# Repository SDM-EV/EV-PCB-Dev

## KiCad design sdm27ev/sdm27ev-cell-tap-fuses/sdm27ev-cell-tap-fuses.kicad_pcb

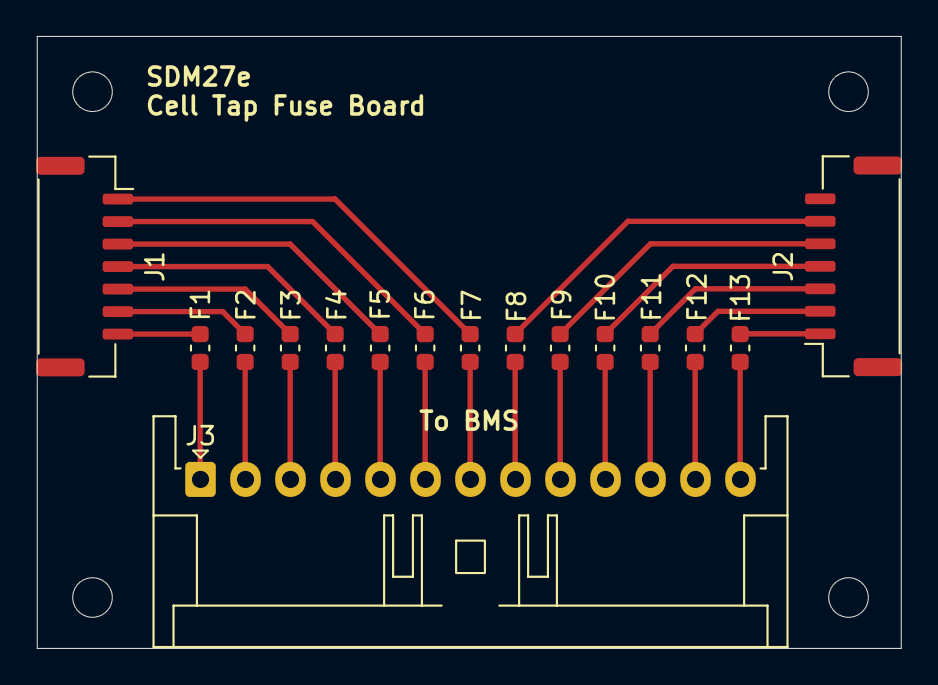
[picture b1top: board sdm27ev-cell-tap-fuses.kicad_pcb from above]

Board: 2 copper layers, 48.0 x 34.0 mm, 20 parts (0 on the bottom side), 26 nets.

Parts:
F1, F2, F3, F4, F5, F6, F7, F8, F9, F10, F11, F12, F13: C_0603_1608Metric
H1, H2, H3, H4: MountingHole; MountingHole_2.2mm_M2
J1, J2: SM07B-GHS-TB; JST_GH_SM07B-GHS-TB_1x07-1MP_P1.25mm_Horizontal
J3: S13B-XASK-1; JST_XA_S13B-XASK-1_1x13_P2.50mm_Horizontal

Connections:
unnamed: F1.1, J1.7
unnamed: F2.1, J1.6
unnamed: F3.1, J1.5
unnamed: F4.1, J1.4
unnamed: F5.1, J1.3
unnamed: F6.1, J1.2
unnamed: F7.1, J1.1
unnamed: F8.1, J2.6
unnamed: F9.1, J2.5
unnamed: F10.1, J2.4
unnamed: F11.1, J2.3
unnamed: F12.1, J2.2
unnamed: F13.1, J2.1
unnamed: F1.2, J3.1
unnamed: F2.2, J3.2
unnamed: F3.2, J3.3
unnamed: F4.2, J3.4
unnamed: F5.2, J3.5
unnamed: F6.2, J3.6
unnamed: F7.2, J3.7
unnamed: F8.2, J3.8
unnamed: F9.2, J3.9
unnamed: F10.2, J3.10
unnamed: F11.2, J3.11
unnamed: F12.2, J3.12
unnamed: F13.2, J3.13

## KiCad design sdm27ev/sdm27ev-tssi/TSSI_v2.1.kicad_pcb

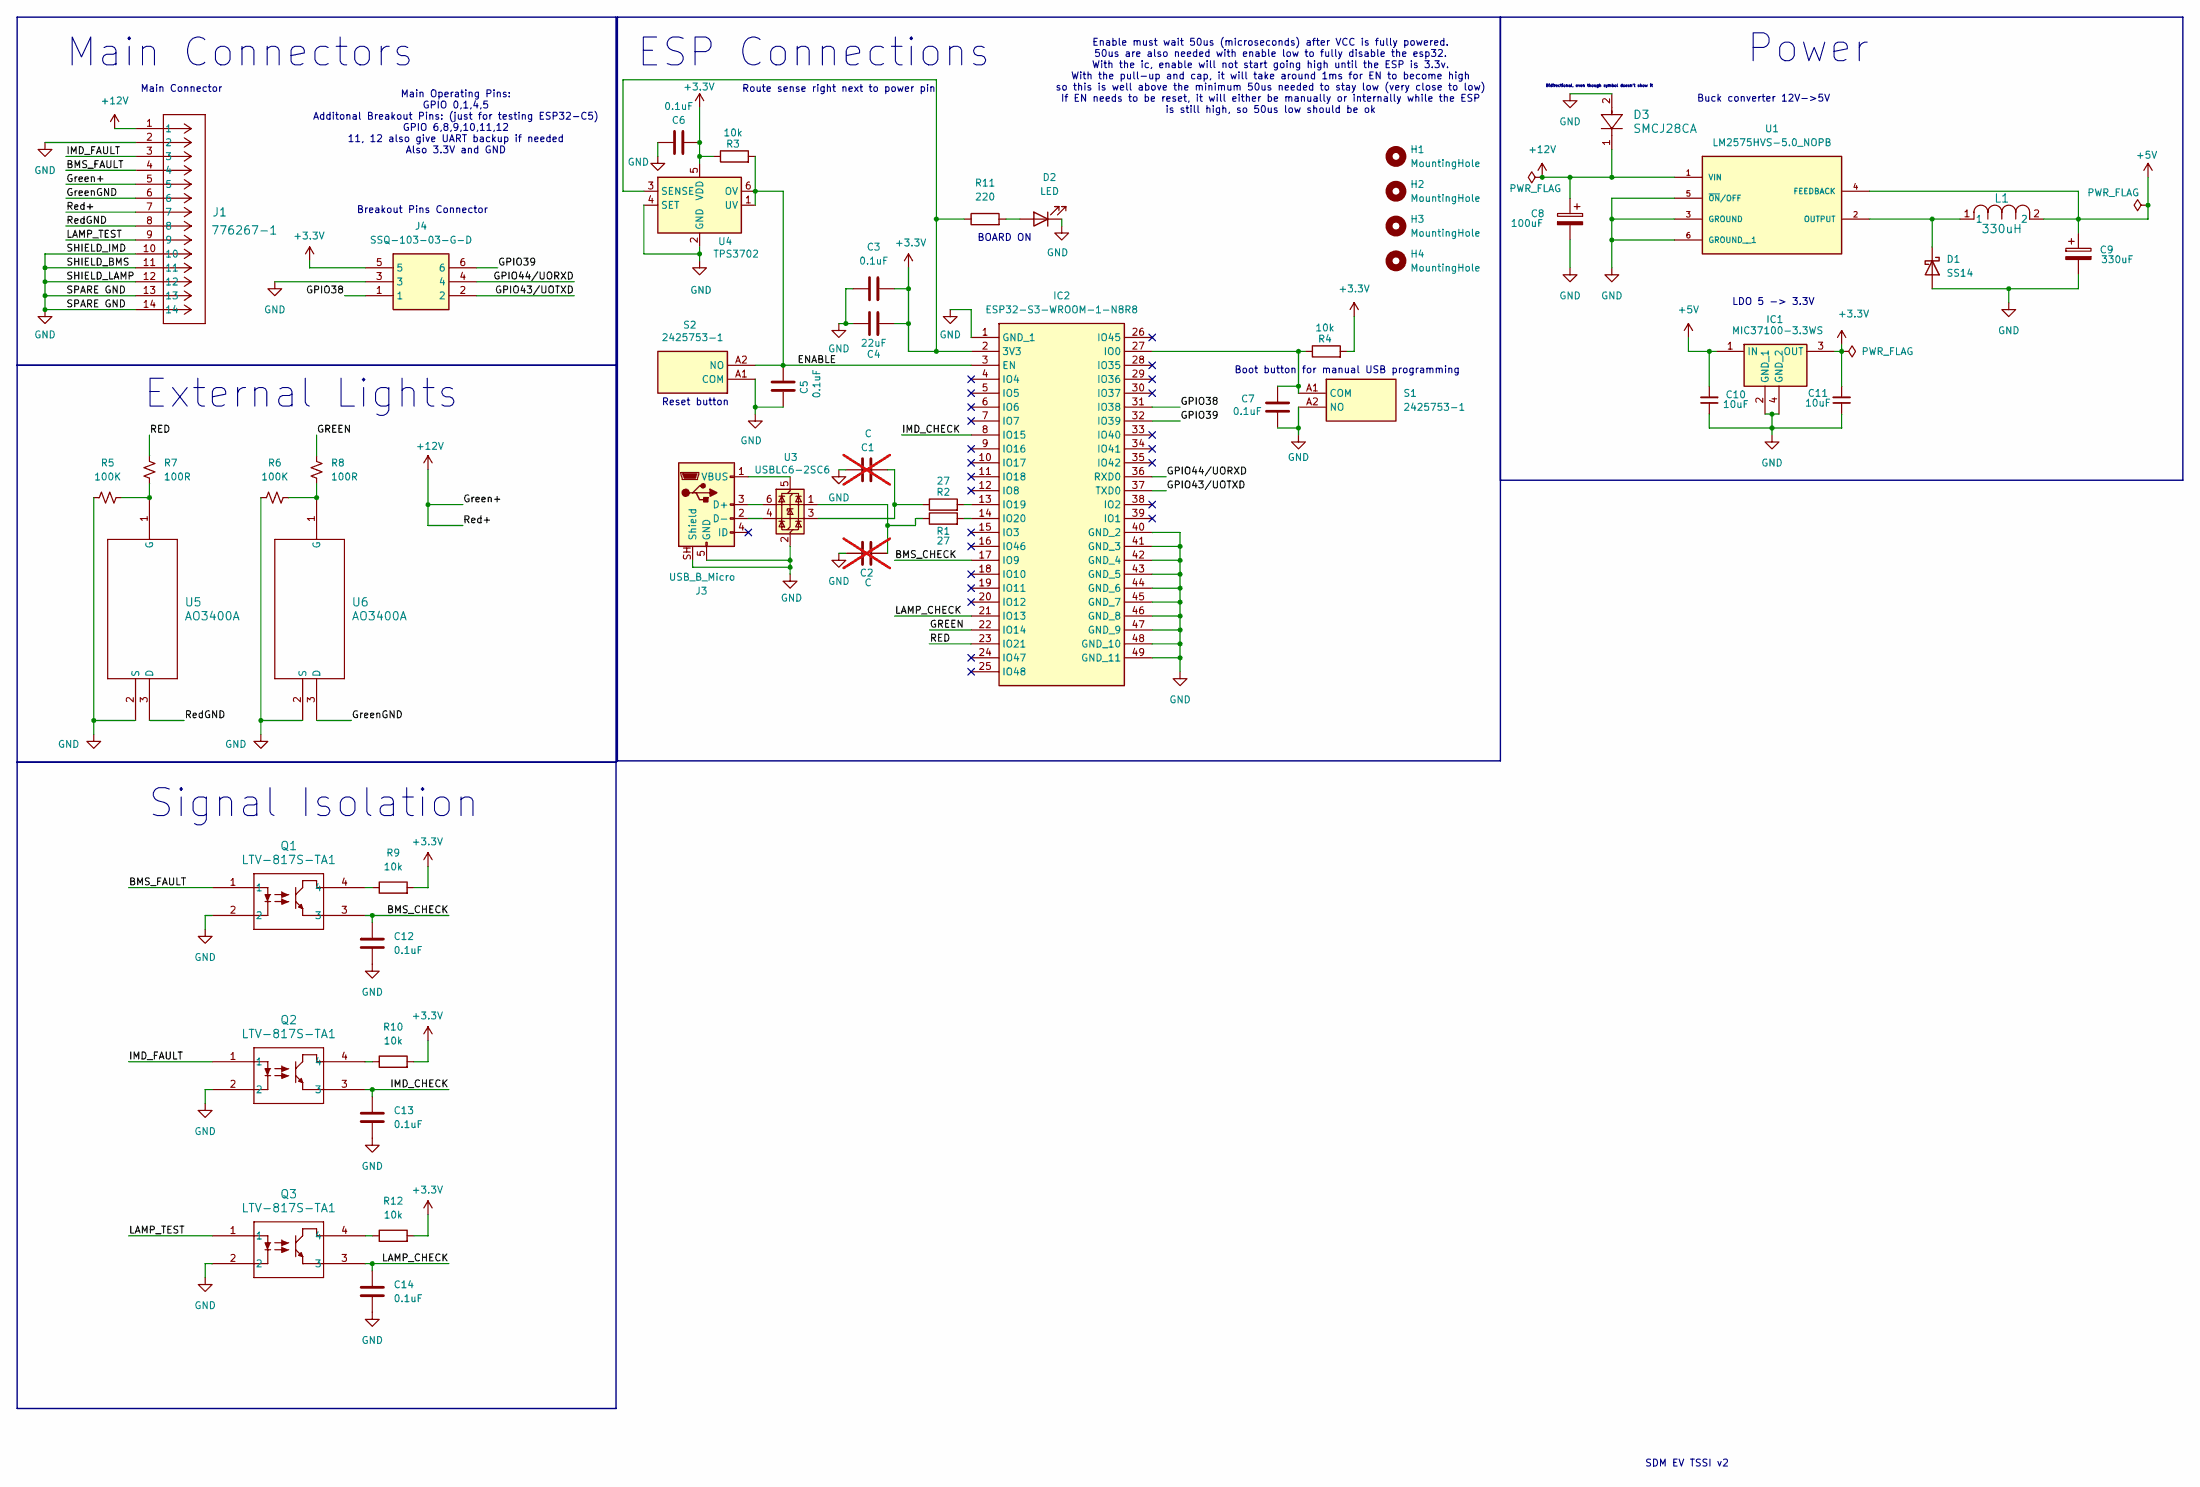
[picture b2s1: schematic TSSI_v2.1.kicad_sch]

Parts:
C1, C2: C; C_0603_1608Metric; not fitted
C3, C5, C6, C7, C12, C13, C14: 0.1uF; C_0603_1608Metric
C4: 22uF; C_0603_1608Metric
C8: 100uF; WCAP-ASLI_6.3X7.7_DXL_
C9: 330uF; CP_Elec_10x10
C10, C11: 10uF; C_0603_1608Metric
D1: SS14; D_SMA
D2: LED; LED_0603_1608Metric
D3: SMCJ28CA; SMCJSeries_LTF
H1, H2, H3, H4: MountingHole; MountingHole_2.2mm_M2
IC1: MIC37100-3.3WS; SOT-223; Mouser Part Number 998-MIC37100-3.3WS
IC2: ESP32-S3-WROOM-1-N8R8; XCVR_ESP32S3WROOM1N8R8; Mouser Part Number 356-EP32S3WROOM1N8R8
J1: 776267-1; CONN14_776267_TEC
J3: USB_B_Micro; USB_Micro-B_Molex-105017-0001
J4: SSQ-103-03-G-D; SSQ-103-XX-YYY-D; Mouser Part Number 200-SSQ10303GD
L1: 330uH; IND_SPD127R_API
Q1, Q2, Q3: LTV-817S-TA1; LTV-817S_LTO
R1, R2: 27; R_0603_1608Metric
R3, R4, R9, R10, R12: 10k; R_0603_1608Metric
R5, R6: 100K; R_0603_1608Metric_Pad0.98x0.95mm_HandSolder
R7, R8: 100R; R_0603_1608Metric_Pad0.98x0.95mm_HandSolder
R11: 220; R_0603_1608Metric
S1, S2: 2425753-1; 24257531; Mouser Part Number 655-2425753-1
U1: LM2575HVS-5.0_NOPB; VREG_LM2575HVS-5.0_NOPB; PARTREV E
U3: USBLC6-2SC6; SOT-23-6
U4: TPS3702; SOT-23-6
U5, U6: AO3400A; SOT-23-3L_AOS

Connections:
+3.3V: C3.2, C4.2, C6.1, C11.2, IC1.3 (OUT), IC2.2 (3V3), J4.5, R3.1, R4.2, R9.2, R10.2, R11.1, R12.2, U4.3 (SENSE), U4.5 (VDD)
+5V: C9.1, C10.2, IC1.1 (IN), L1.2, U1.4 (FEEDBACK)
+12V: C8.1, D3.1, J1.1, J1.5, J1.7, U1.1 (VIN)
/BMS_CHECK: C12.1, IC2.17 (IO9), Q1.3
/BMS_FAULT: J1.4, Q1.1
/ENABLE: C5.1, IC2.3 (EN), R3.2, S2.A2 (NO), U4.1 (UV), U4.6 (OV)
/GPIO38: IC2.31 (IO38), J4.1
/GPIO39: IC2.32 (IO39), J4.6
/GPIO43/UOTXD: IC2.37 (TXD0), J4.2
/GPIO44/UORXD: IC2.36 (RXD0), J4.4
/GREEN: IC2.22 (IO14), R8.1
/GreenGND: J1.6, U6.3 (D)
/IMD_CHECK: C13.1, IC2.8 (IO15), Q2.3
/IMD_FAULT: J1.3, Q2.1
/LAMP_CHECK: C14.1, IC2.21 (IO13), Q3.3
/LAMP_TEST: J1.9, Q3.1
/RED: IC2.23 (IO21), R7.1
/RedGND: J1.8, U5.3 (D)
GND: C1.1, C2.1, C3.1, C4.1, C5.2, C6.2, C7.1, C8.2, C9.2, C10.1, C11.1, C12.2, C13.2, C14.2, D1.2 (A), D2.1 (K), D3.2, IC1.2 (GND_1), IC1.4 (GND_2), IC2.1 (GND_1), IC2.40 (GND_2), IC2.41 (GND_3), IC2.42 (GND_4), IC2.43 (GND_5), IC2.44 (GND_6), IC2.45 (GND_7), IC2.46 (GND_8), IC2.47 (GND_9), IC2.48 (GND_10), IC2.49 (GND_11), J1.2, J1.10, J1.11, J1.12, J1.13, J1.14, J3.5 (GND), J3.SH (Shield), J4.3, Q1.2, Q2.2, Q3.2, R5.1, R6.1, S1.A2 (NO), S2.A1 (COM), U1.3 (GROUND), U1.5 (~ON/OFF), U1.6 (GROUND__1), U3.2 (GND), U4.2 (GND), U4.4 (SET), U5.2 (S), U6.2 (S)
unnamed: C1.2, R2.1, U3.3 (I/O2)
unnamed: C2.2, R1.1, U3.1 (I/O1)
unnamed: D1.1 (K), L1.1, U1.2 (OUTPUT)
unnamed: D2.2 (A), R11.2
unnamed: C7.2, IC2.27 (IO0), R4.1, S1.A1 (COM)
unnamed: IC2.13 (IO19), R2.2
unnamed: IC2.14 (IO20), R1.2
unnamed: J3.3 (D+), U3.6 (I/O1)
unnamed: J3.2 (D-), U3.4 (I/O2)
unnamed: J3.1 (VBUS), U3.5 (VBUS)
unnamed: Q1.4, R9.1
unnamed: Q2.4, R10.1
unnamed: Q3.4, R12.1
unnamed: R5.2, R7.2, U5.1 (G)
unnamed: R6.2, R8.2, U6.1 (G)

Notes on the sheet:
LDO 5 -> 3.3V
SDM EV TSSI v2
Reset button
Buck converter 12V->5V
Bidirectional, even though symbol doesn't show it
Signal Isolation
Main Operating Pins: GPIO 0,1,4,5 Additonal Breakout Pins: (just for testing ESP32-C5) GPIO 6,8,9,10,11,12 11, 12 also give UART backup if needed Also 3.3V and GND
Power
ESP Connections
External Lights
Route sense right next to power pin
Enable must wait 50us (microseconds) after VCC is fully powered. 50us are also needed with enable low to fully disable the esp32. With the ic, enable will not start going high until the ESP is 3.3v. With the pull-up and cap, it will take around 1ms for EN to become high so this is well above the mi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
Main Connector
BOARD ON
Main Connectors
Breakout Pins Connector
Boot button for manual USB programming

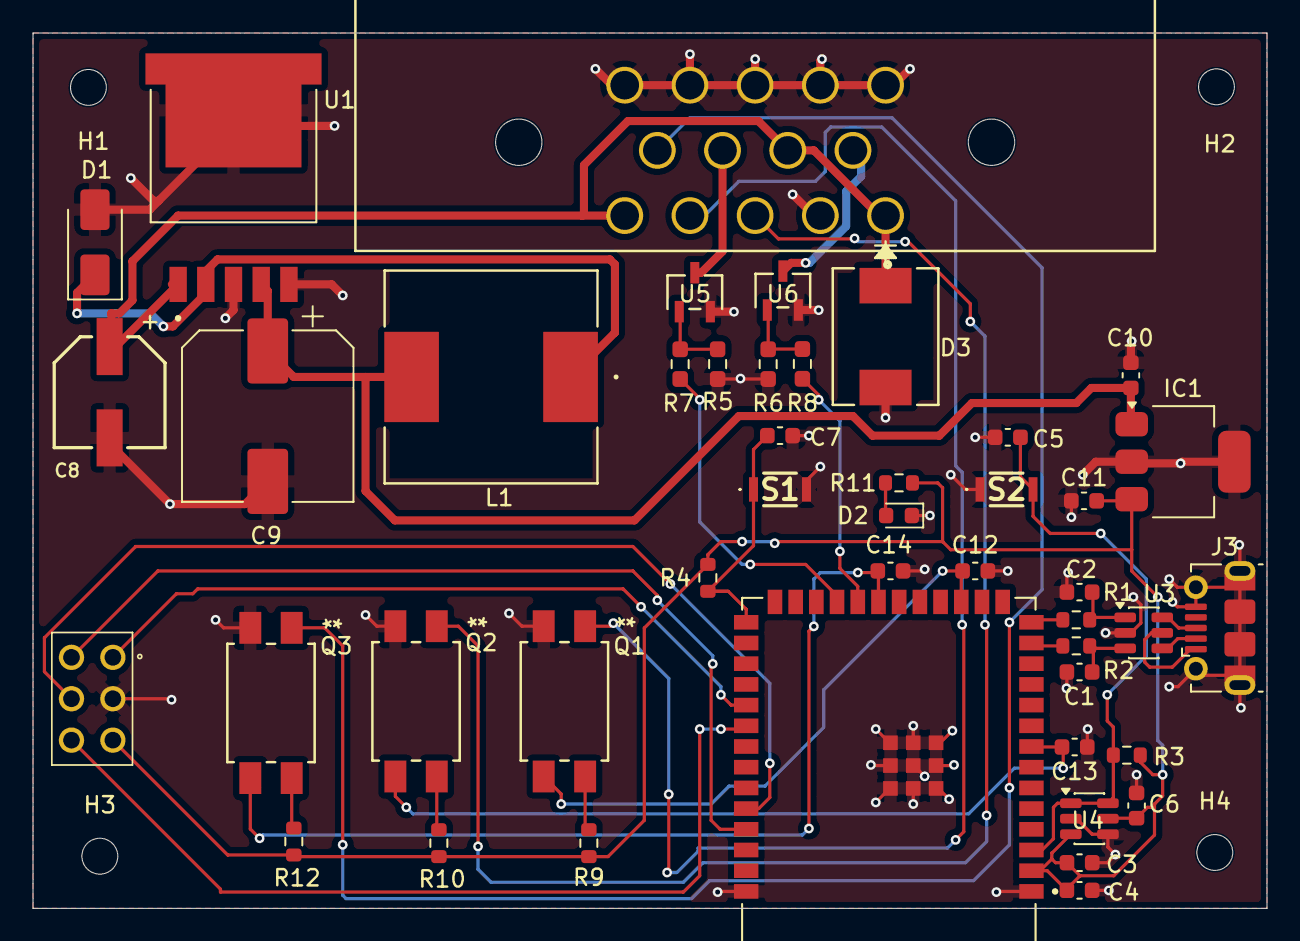
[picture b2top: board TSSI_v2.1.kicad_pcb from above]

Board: 2 copper layers, 75.7 x 53.7 mm, 49 parts (0 on the bottom side), 34 nets.

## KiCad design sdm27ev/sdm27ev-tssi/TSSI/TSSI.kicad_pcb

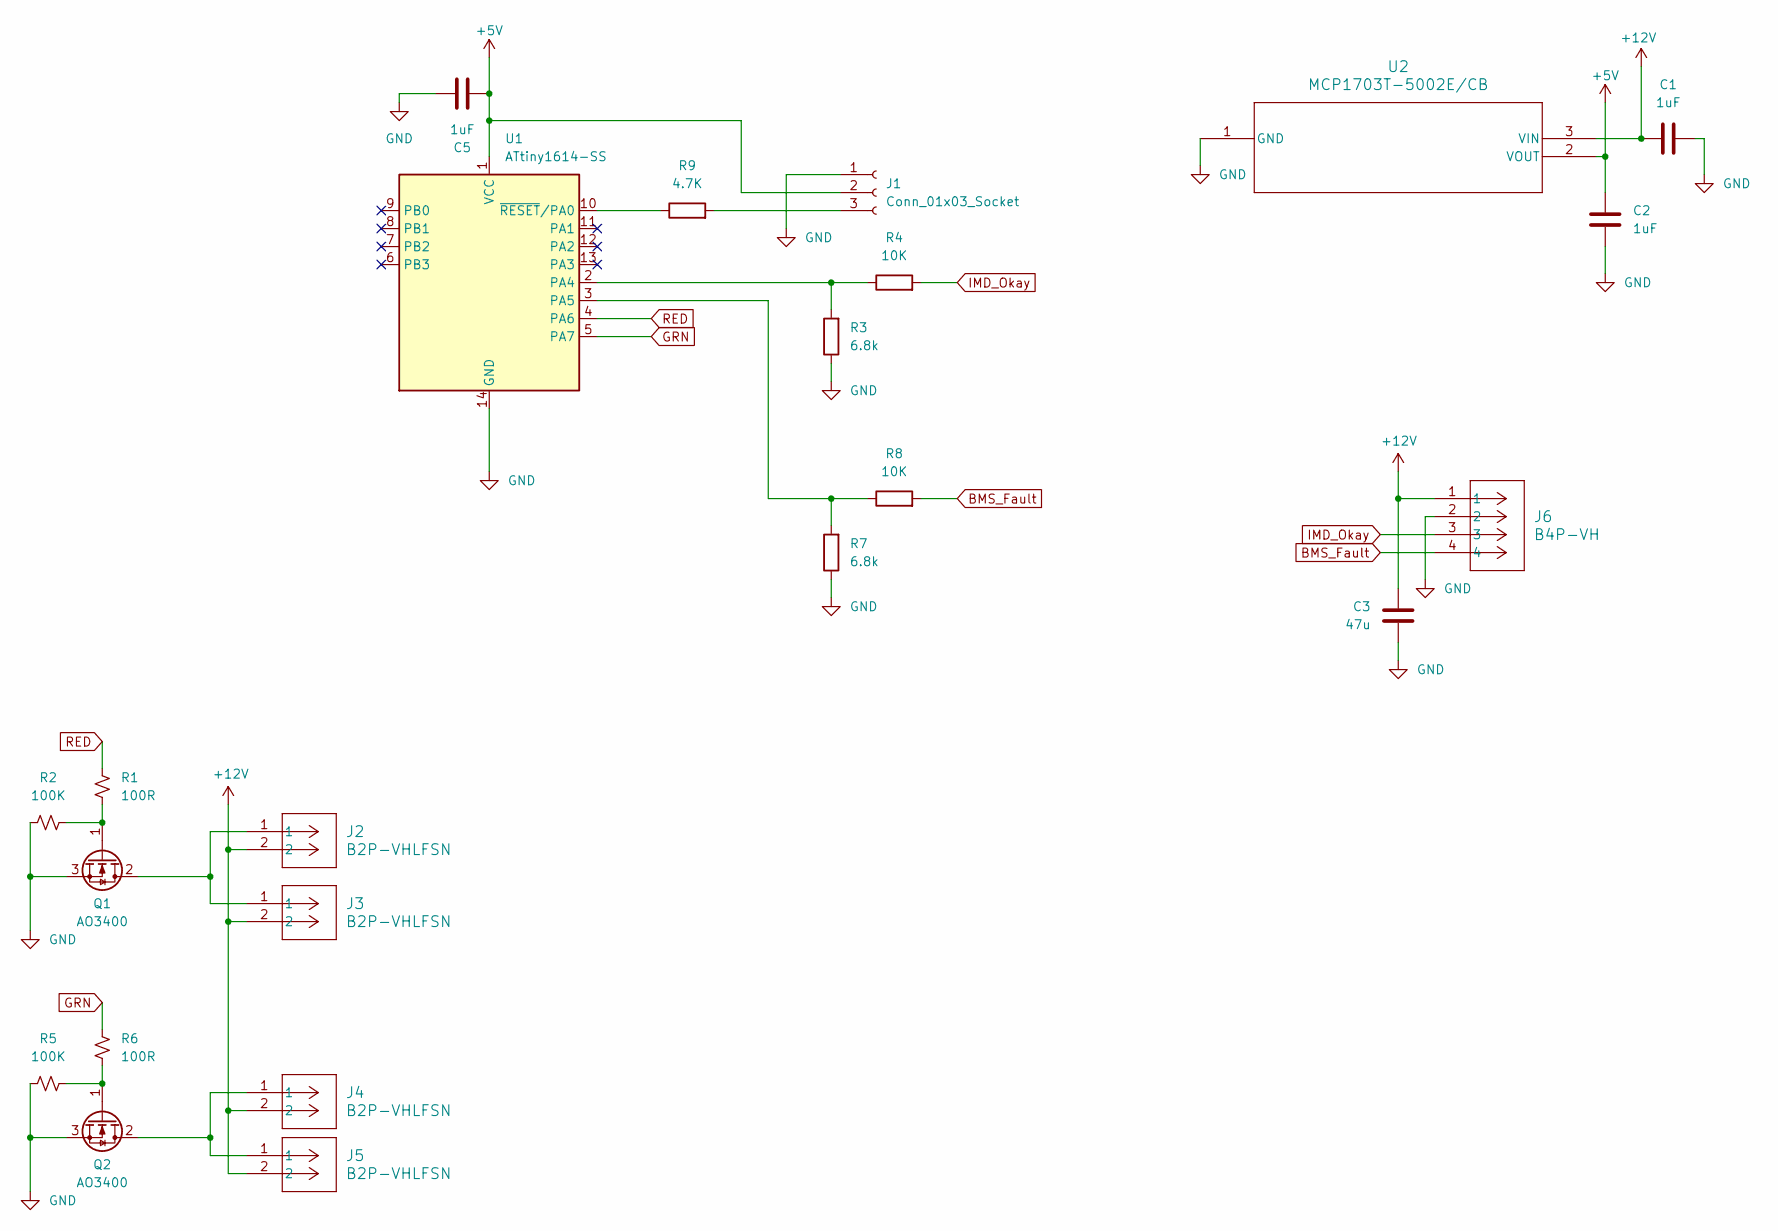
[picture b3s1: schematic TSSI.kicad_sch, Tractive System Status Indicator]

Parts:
C1, C2, C5: 1uF; C_0603_1608Metric_Pad1.08x0.95mm_HandSolder
C3: 47u; CP_Wurth_WCAP-ASLI-D5L5.5
J1: Conn_01x03_Socket; PinHeader_1x03_P2.54mm_Vertical
J2, J3, J4, J5: B2P-VHLFSN; CONN_B2P-VH_JST
J6: B4P-VH; CONN_B4P-VH_JST
Q1, Q2: AO3400; SOT-23-3L_AOS
R1, R6: 100R; R_0603_1608Metric_Pad0.98x0.95mm_HandSolder
R2, R5: 100K; R_0603_1608Metric_Pad0.98x0.95mm_HandSolder
R3, R7: 6.8k; R_0603_1608Metric_Pad0.98x0.95mm_HandSolder
R4, R8: 10K; R_0603_1608Metric_Pad0.98x0.95mm_HandSolder
R9: 4.7K; R_0603_1608Metric_Pad0.98x0.95mm_HandSolder
U1: ATtiny1614-SS; SOIC-14_3.9x8.7mm_P1.27mm
U2: MCP1703T-5002E/CB; SOT-23A_MC_MCH

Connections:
+5V: C2.2, C5.1, J1.2, U1.1 (VCC), U2.2 (VOUT)
+12V: C1.1, C3.2, J2.2, J3.2, J4.2, J5.2, J6.1, U2.3 (VIN)
BMS_Fault: J6.4, R8.2
GND: C1.2, C2.1, C3.1, C5.2, J1.1, J6.2, Q1.3 (S), Q2.3 (S), R2.1, R3.1, R5.1, R7.1, U1.14 (GND), U2.1 (GND)
GRN: R6.1, U1.5 (PA7)
IMD_Okay: J6.3, R4.2
unnamed: J1.3, R9.2
unnamed: J2.1, J3.1, Q1.2 (D)
unnamed: Q1.1 (G), R1.2, R2.2
unnamed: J4.1, J5.1, Q2.2 (D)
unnamed: Q2.1 (G), R5.2, R6.2
unnamed: R3.2, R4.1, U1.2 (PA4)
unnamed: R7.2, R8.1, U1.3 (PA5)
unnamed: R9.1, U1.10 (~RESET/PA0)
RED: R1.1, U1.4 (PA6)

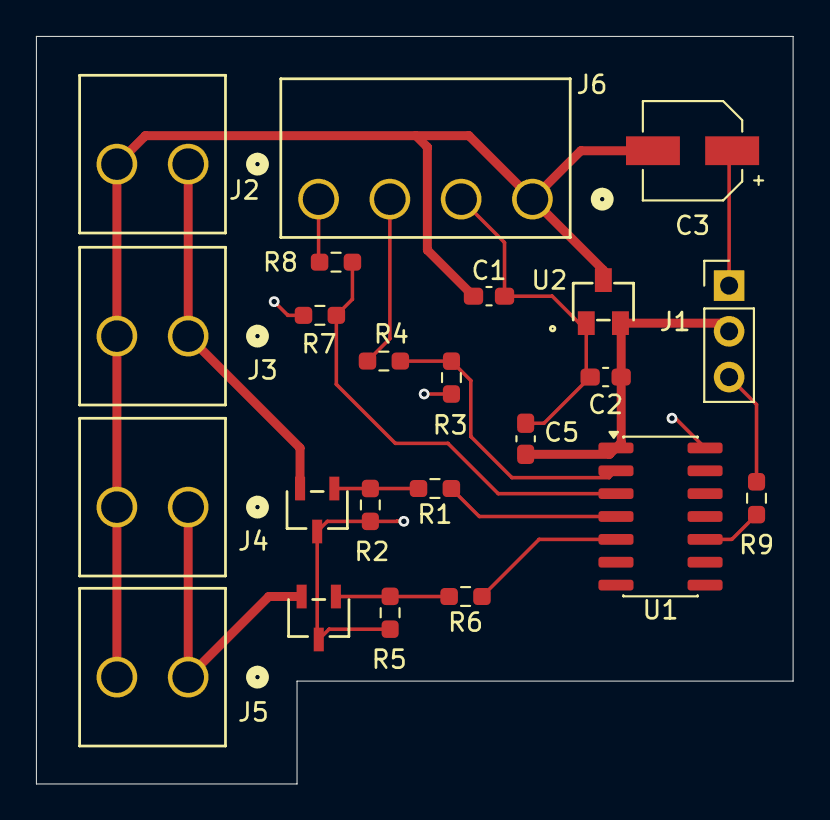
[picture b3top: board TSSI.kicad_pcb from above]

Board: 2 copper layers, 42.0 x 41.5 mm, 23 parts (0 on the bottom side), 15 nets.

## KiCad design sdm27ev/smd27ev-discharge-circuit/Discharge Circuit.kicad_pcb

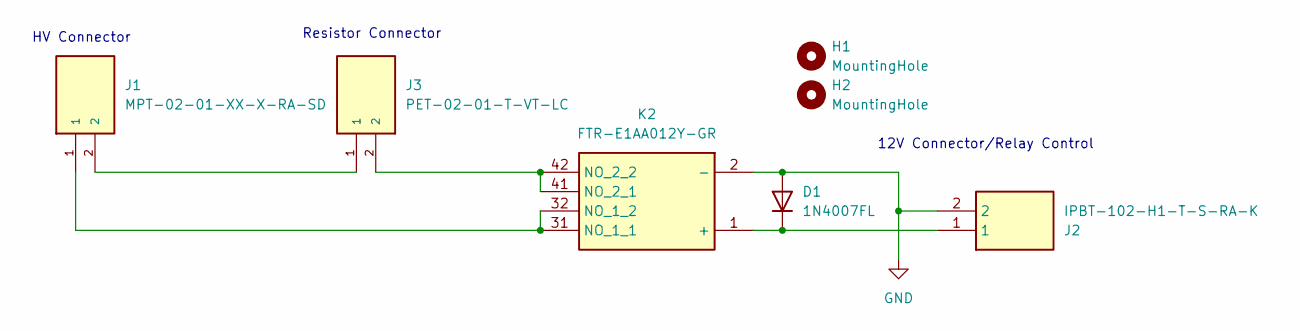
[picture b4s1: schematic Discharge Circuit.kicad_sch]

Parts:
D1: 1N4007FL; D_SOD-123F
H1, H2: MountingHole; MountingHole_3.2mm_M3
J1: MPT-02-01-XX-X-RA-SD; SAMTEC_MPT-02-01-XX-X-RA-SD; PARTREV B
J2: IPBT-102-H1-T-S-RA-K; IPBT102H1TSRAK; Mouser Part Number 200-IPBT102H1TSRAK
J3: PET-02-01-T-VT-LC; SAMTEC_PET-02-XX-X-VT-LC; PARTREV C
K2: FTR-E1AA012Y-GR; FTRE1AA012YGR; Mouser Part Number 817-FTR-E1AA012Y-GR

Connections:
GND: D1.2 (A), J2.2, K2.2 (-)
unnamed: D1.1 (K), J2.1, K2.1 (+)
unnamed: J1.2, J3.1
unnamed: J1.1, K2.31 (NO_1_1), K2.32 (NO_1_2)
unnamed: J3.2, K2.41 (NO_2_1), K2.42 (NO_2_2)

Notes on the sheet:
Resistor Connector
12V Connector/Relay Control
HV Connector

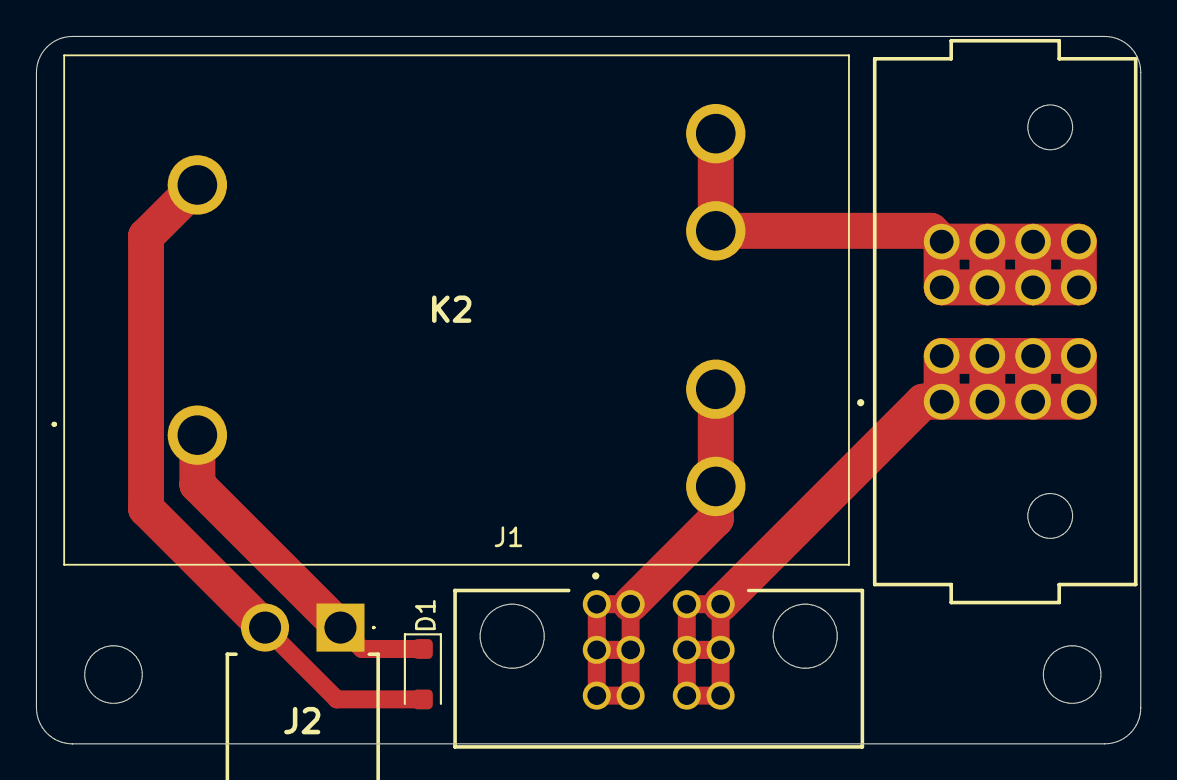
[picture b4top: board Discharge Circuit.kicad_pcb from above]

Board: 2 copper layers, 61.3 x 39.3 mm, 7 parts (0 on the bottom side), 5 nets.

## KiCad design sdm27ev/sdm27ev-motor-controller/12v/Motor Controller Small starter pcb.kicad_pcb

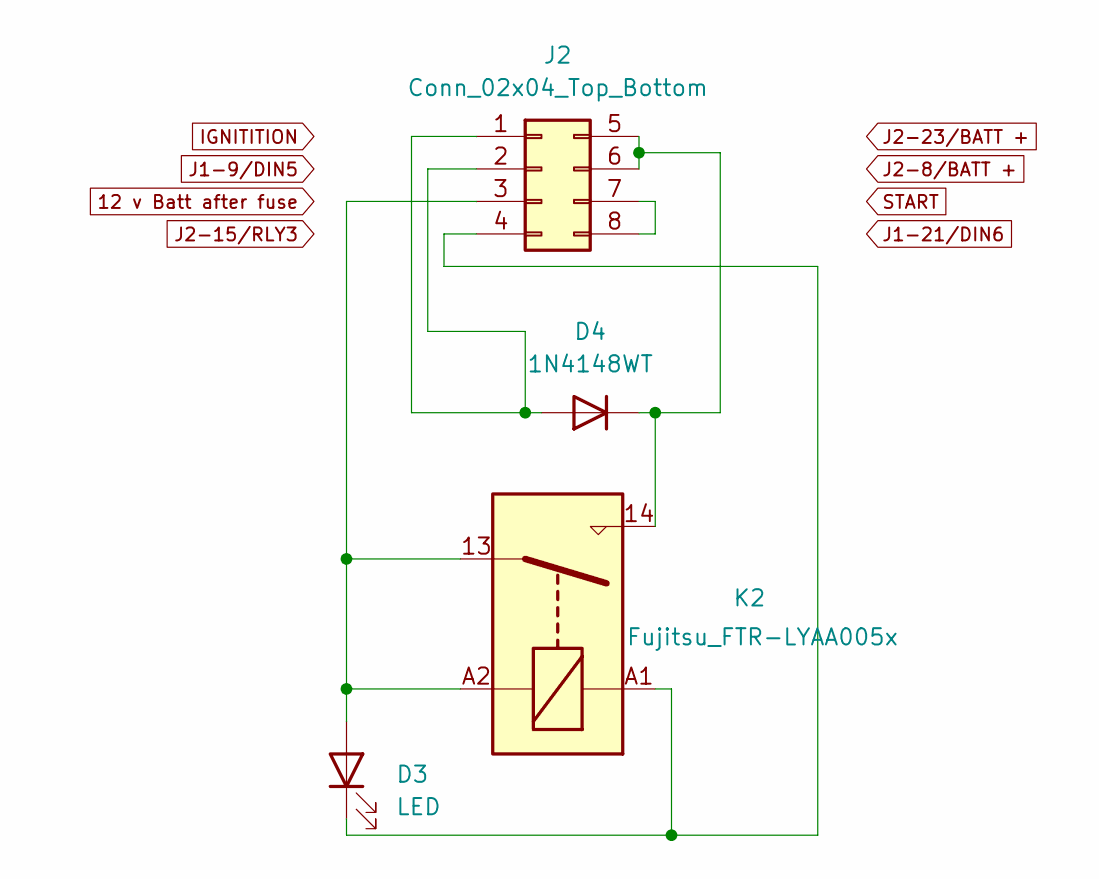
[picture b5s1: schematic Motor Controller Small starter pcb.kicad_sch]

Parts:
D3: LED; LED_D3.0mm
D4: 1N4148WT; D_SOD-523
J2: Conn_02x04_Top_Bottom; Molex_Mini-Fit_Jr_5566-08A2_2x04_P4.20mm_Vertical
K2: Fujitsu_FTR-LYAA005x; Relay_SPST-NO_Fujitsu_FTR-LYAA005x_FormA_Vertical

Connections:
unnamed: D3.2 (A), J2.3, K2.13, K2.A2
unnamed: D3.1 (K), J2.4, K2.A1
unnamed: D4.2 (A), J2.1, J2.2
unnamed: D4.1 (K), J2.5, J2.6, K2.14
unnamed: J2.7, J2.8

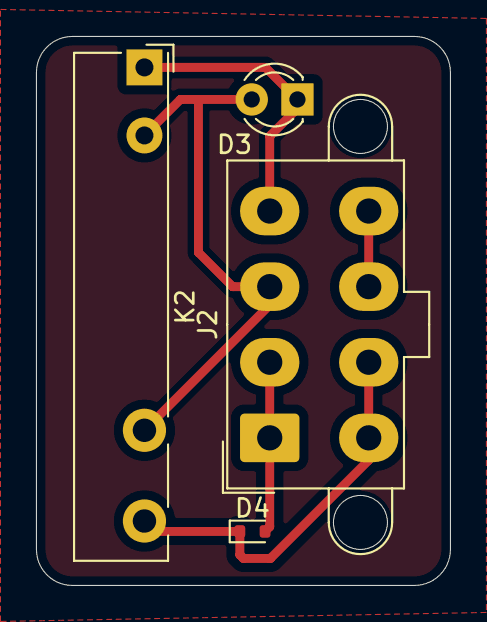
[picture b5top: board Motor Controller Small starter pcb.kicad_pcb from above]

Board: 2 copper layers, 23.0 x 30.5 mm, 4 parts (0 on the bottom side), 5 nets.
